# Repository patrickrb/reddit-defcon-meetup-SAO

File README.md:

# reddit-defcon-meetup-SAO
SAO for reddit meetup at Defcon 27

It has a CR2032 coin cell battery as well as a shitty add on connector....probably not a good idea to use both at once.  This is a *shitty* add on after all.

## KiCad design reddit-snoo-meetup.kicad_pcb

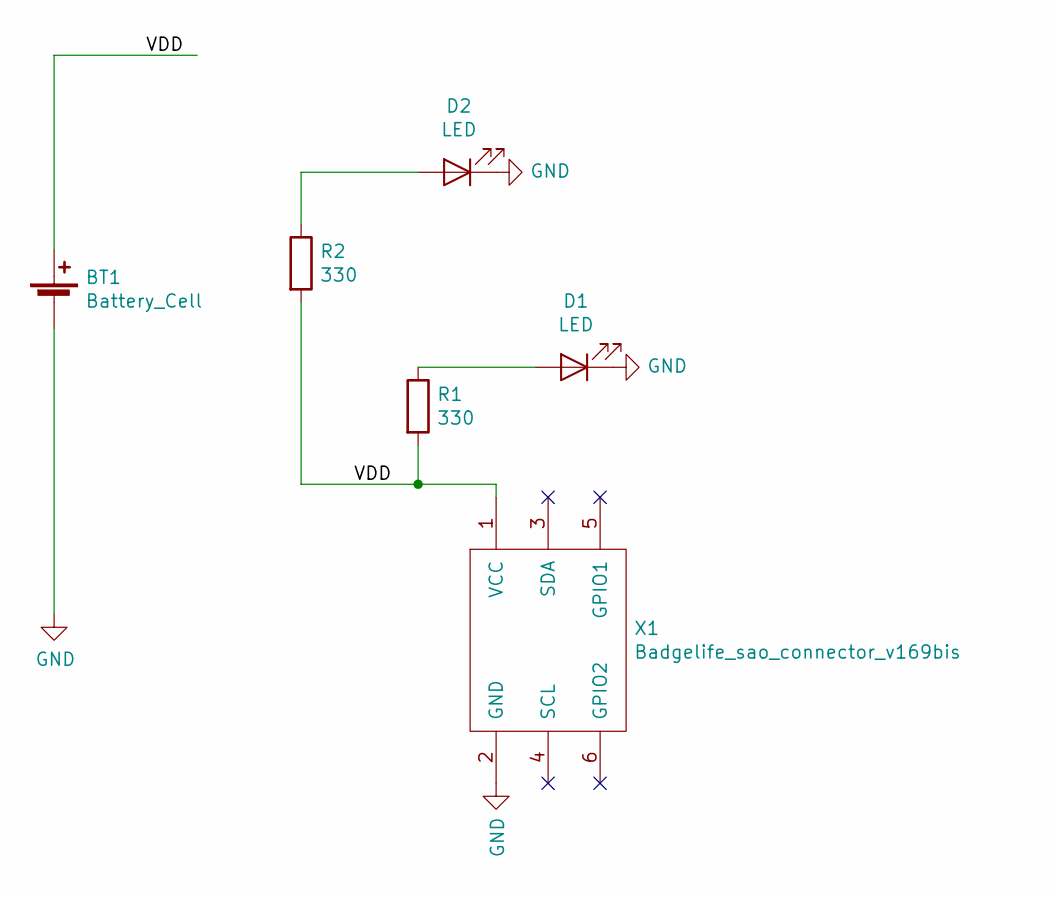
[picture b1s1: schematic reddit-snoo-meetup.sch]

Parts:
BT1: Battery_Cell; BatteryHolder_MPD_BC2003_1x2032
D1, D2: LED; LED_1206_3216Metric
R1, R2: 330; R_1206_3216Metric
X1: Badgelife_sao_connector_v169bis; Badgelife-SAOv169-SAO-2x3

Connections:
/VDD: BT1.1 (+), R1.2, R2.2, X1.1 (VCC)
GND: BT1.2 (-), D1.1 (K), D2.1 (K), X1.2 (GND)
unnamed: D1.2 (A), R1.1
unnamed: D2.2 (A), R2.1

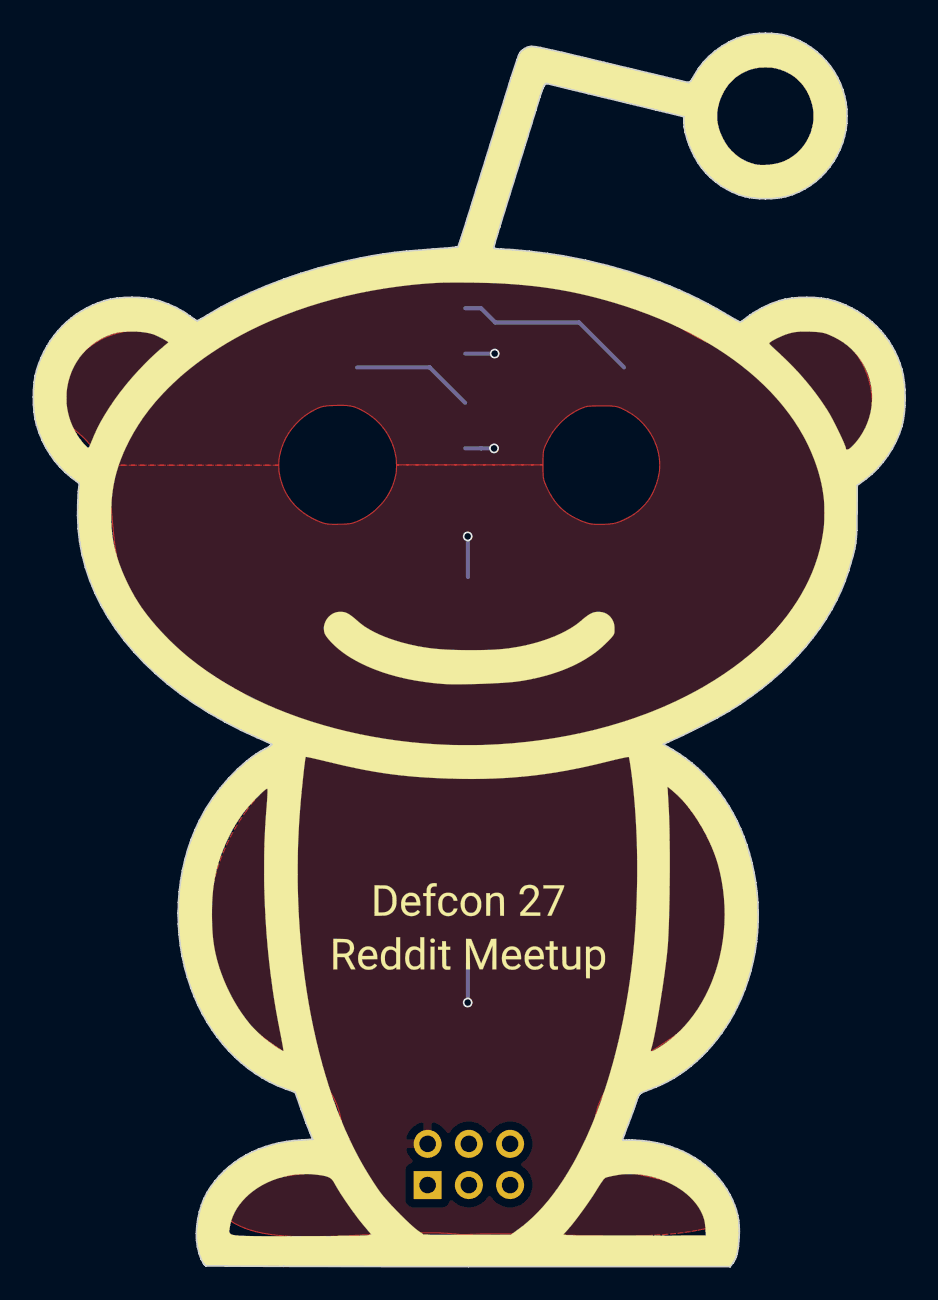
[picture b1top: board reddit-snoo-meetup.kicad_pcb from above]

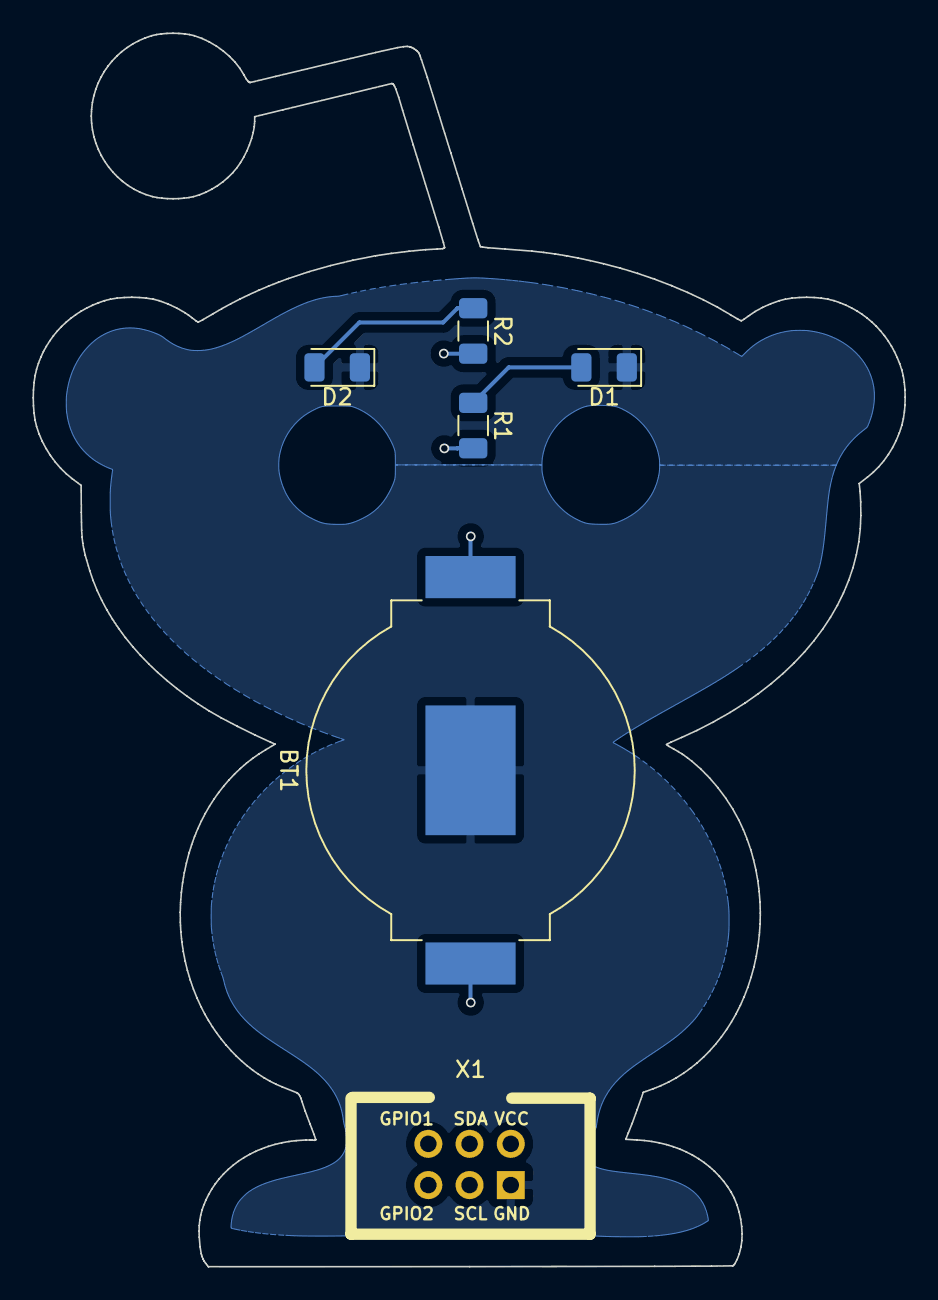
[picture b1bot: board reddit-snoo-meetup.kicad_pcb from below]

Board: 2 copper layers, 53.7 x 76.0 mm, 6 parts (5 on the bottom side), 4 nets.

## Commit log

2019-07-21 added copper layers, need to be converted still to ground and vcc planes
2019-07-21 final i think
2019-07-22 updated gerbers
